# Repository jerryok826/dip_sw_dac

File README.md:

# dip_sw_dac

## Project Description
Dip_sw_dac is an attempt to build a simple but precise digital potentiometer. It takes the VCC input of 5v or 3.3v and produces a selectable output in 64 steps. It can replace a three turn potentiometer in some adjustment use cases. The right most switch selects vcc/2. The left most switch is vcc/64. So for example if the two rightmost switches are on the board will output 3.75 Volts with a 5V VCC. Enabling the leftmost switch will increase the output by 0.078 volts or 1/64 of 5V.

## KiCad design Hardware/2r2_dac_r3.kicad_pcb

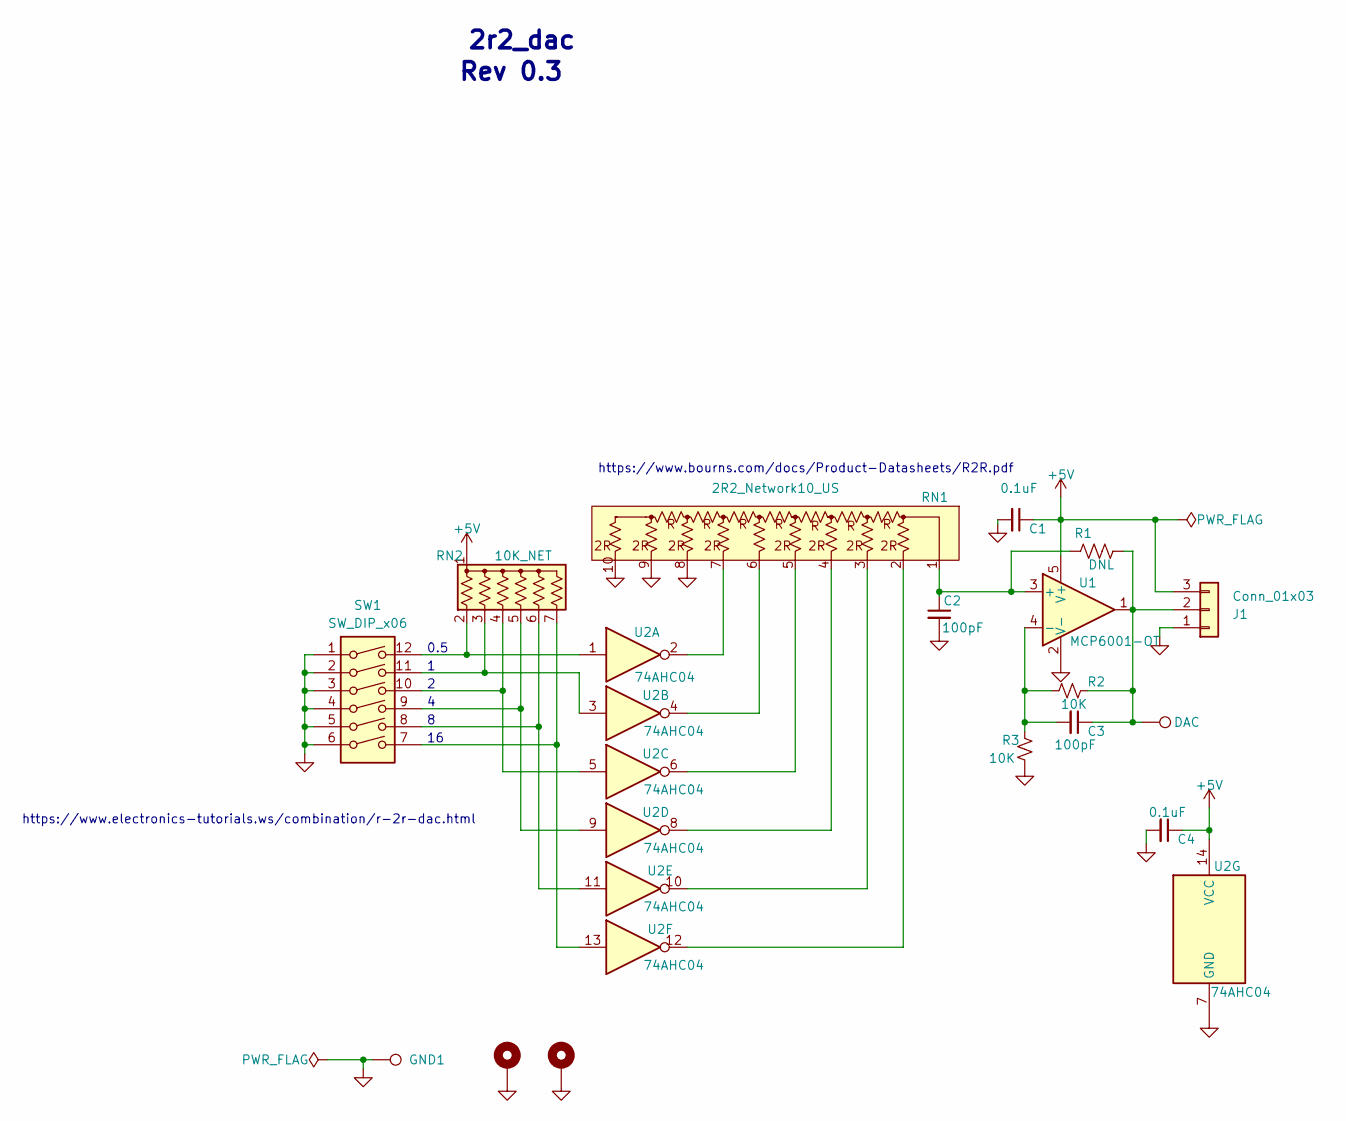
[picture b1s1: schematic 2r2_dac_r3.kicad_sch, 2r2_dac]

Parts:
C1, C4: 0.1uF; C_0603_1608Metric_Pad1.08x0.95mm_HandSolder
C2, C3: 100pF; C_0603_1608Metric_Pad1.08x0.95mm_HandSolder
DAC1: DAC; TestPoint_THTPad_D2.0mm_Drill1.0mm
GND1: GND1; TestPoint_THTPad_D2.0mm_Drill1.0mm
H1, H2: MountingHole_Pad; MountingHole_2.7mm_M2.5_ISO14580_Pad
J1: Conn_01x03; PinHeader_1x03_P2.54mm_Vertical
R1: DNL; R_0603_1608Metric_Pad0.98x0.95mm_HandSolder
R2, R3: 10K; R_0603_1608Metric_Pad0.98x0.95mm_HandSolder
RN1: 2R2_Network10_US; R_Array_SIP10
RN2: 10K_NET; R_Array_SIP7
SW1: SW_DIP_x06; DIP-12_W7.62mm
U1: MCP6001-OT; SOT-23-5
U2: 74AHC04; SOIC-14_3.9x8.7mm_P1.27mm

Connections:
+5V: C1.1, C4.1, J1.3, RN2.1 (common), U1.5 (V+), U2.14 (VCC)
GND: C1.2, C2.2, C4.2, GND1.1, H1.1, H2.1, J1.1, R3.1, RN1.8 (R7), RN1.9 (R8), RN1.10 (R10), SW1.1, SW1.2, SW1.3, SW1.4, SW1.5, SW1.6, U1.2 (V-), U2.7 (GND)
unnamed: C3.1, DAC1.1, J1.2, R1.2, R2.2, U1.1
unnamed: RN1.3 (2), U2.10
unnamed: C2.1, R1.1, RN1.1 (BIT_OUT), U1.3 (+)
unnamed: RN1.2 (MSB_1), U2.12
unnamed: RN1.4 (R3), U2.8
unnamed: RN1.5 (R4), U2.6
unnamed: RN1.6 (R5), U2.4
unnamed: RN1.7 (R6), U2.2
unnamed: RN2.2 (R1), SW1.12, U2.1
unnamed: RN2.3 (R2), SW1.11, U2.3
unnamed: RN2.4 (R3), SW1.10, U2.5
unnamed: RN2.5 (R4), SW1.9, U2.9
unnamed: RN2.6 (R5), SW1.8, U2.11
unnamed: RN2.7 (R6), SW1.7, U2.13
unnamed: C3.2, R2.1, R3.2, U1.4 (-)

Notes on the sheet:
0.5
https://www.bourns.com/docs/Product-Datasheets/R2R.pdf
2r2_dac
Rev 0.3
https://www.electronics-tutorials.ws/combination/r-2r-dac.html

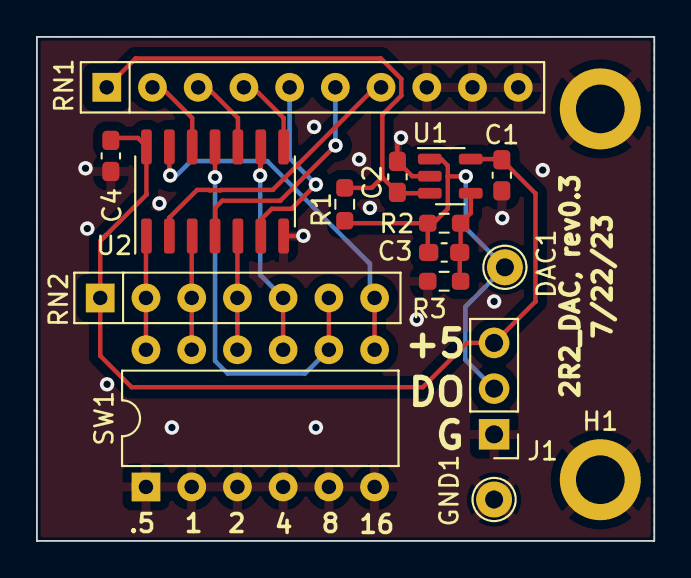
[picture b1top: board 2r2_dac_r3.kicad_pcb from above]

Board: 2 copper layers, 34.3 x 28.0 mm, 17 parts (0 on the bottom side), 17 nets.

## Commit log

2024-02-07 update photos
